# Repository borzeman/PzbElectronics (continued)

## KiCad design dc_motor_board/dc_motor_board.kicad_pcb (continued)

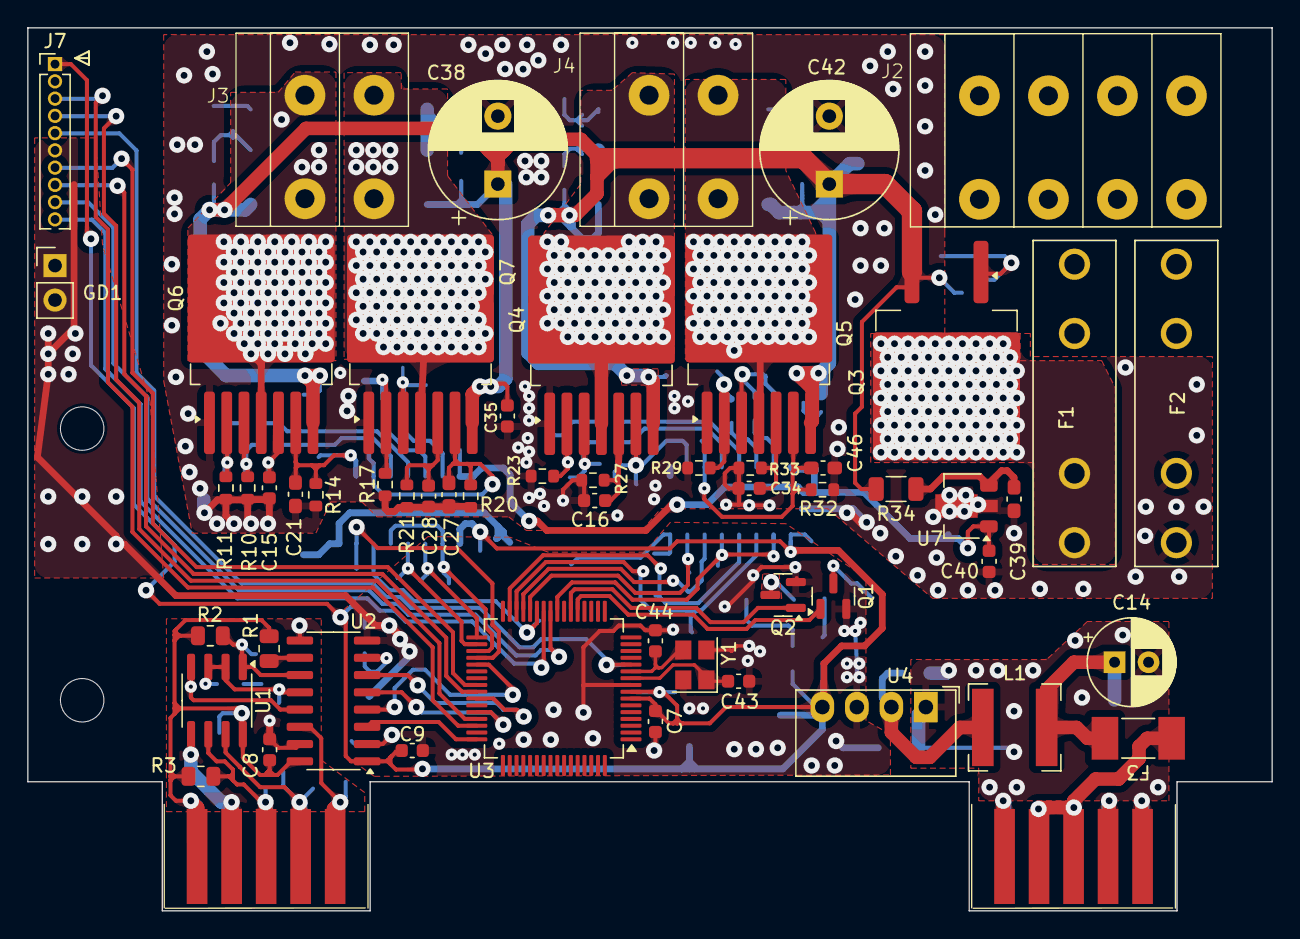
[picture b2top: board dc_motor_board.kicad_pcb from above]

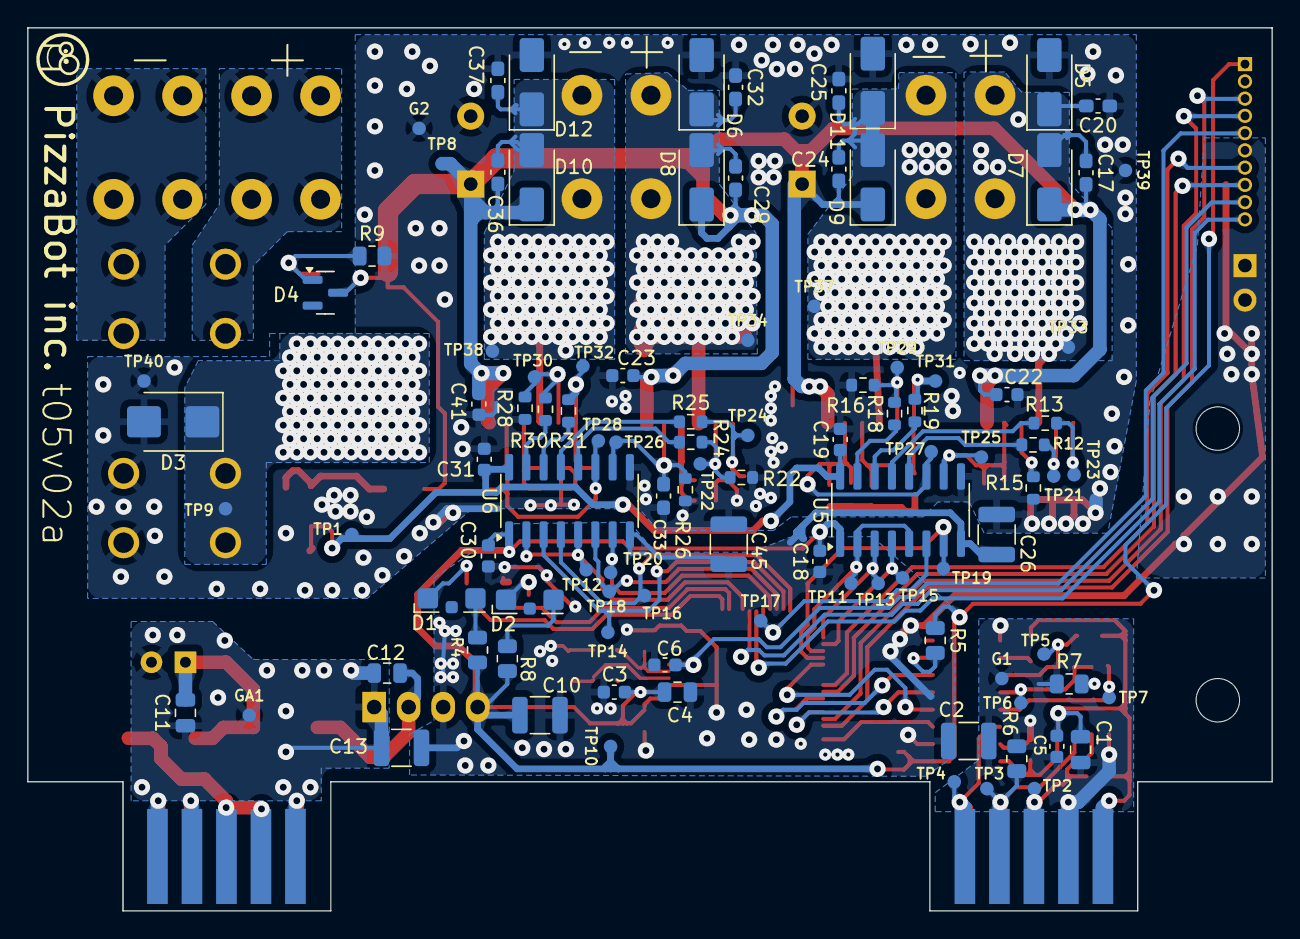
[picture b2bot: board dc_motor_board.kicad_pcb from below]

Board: 2 copper layers, 91.6 x 65.0 mm, 161 parts (102 on the bottom side), 81 nets.

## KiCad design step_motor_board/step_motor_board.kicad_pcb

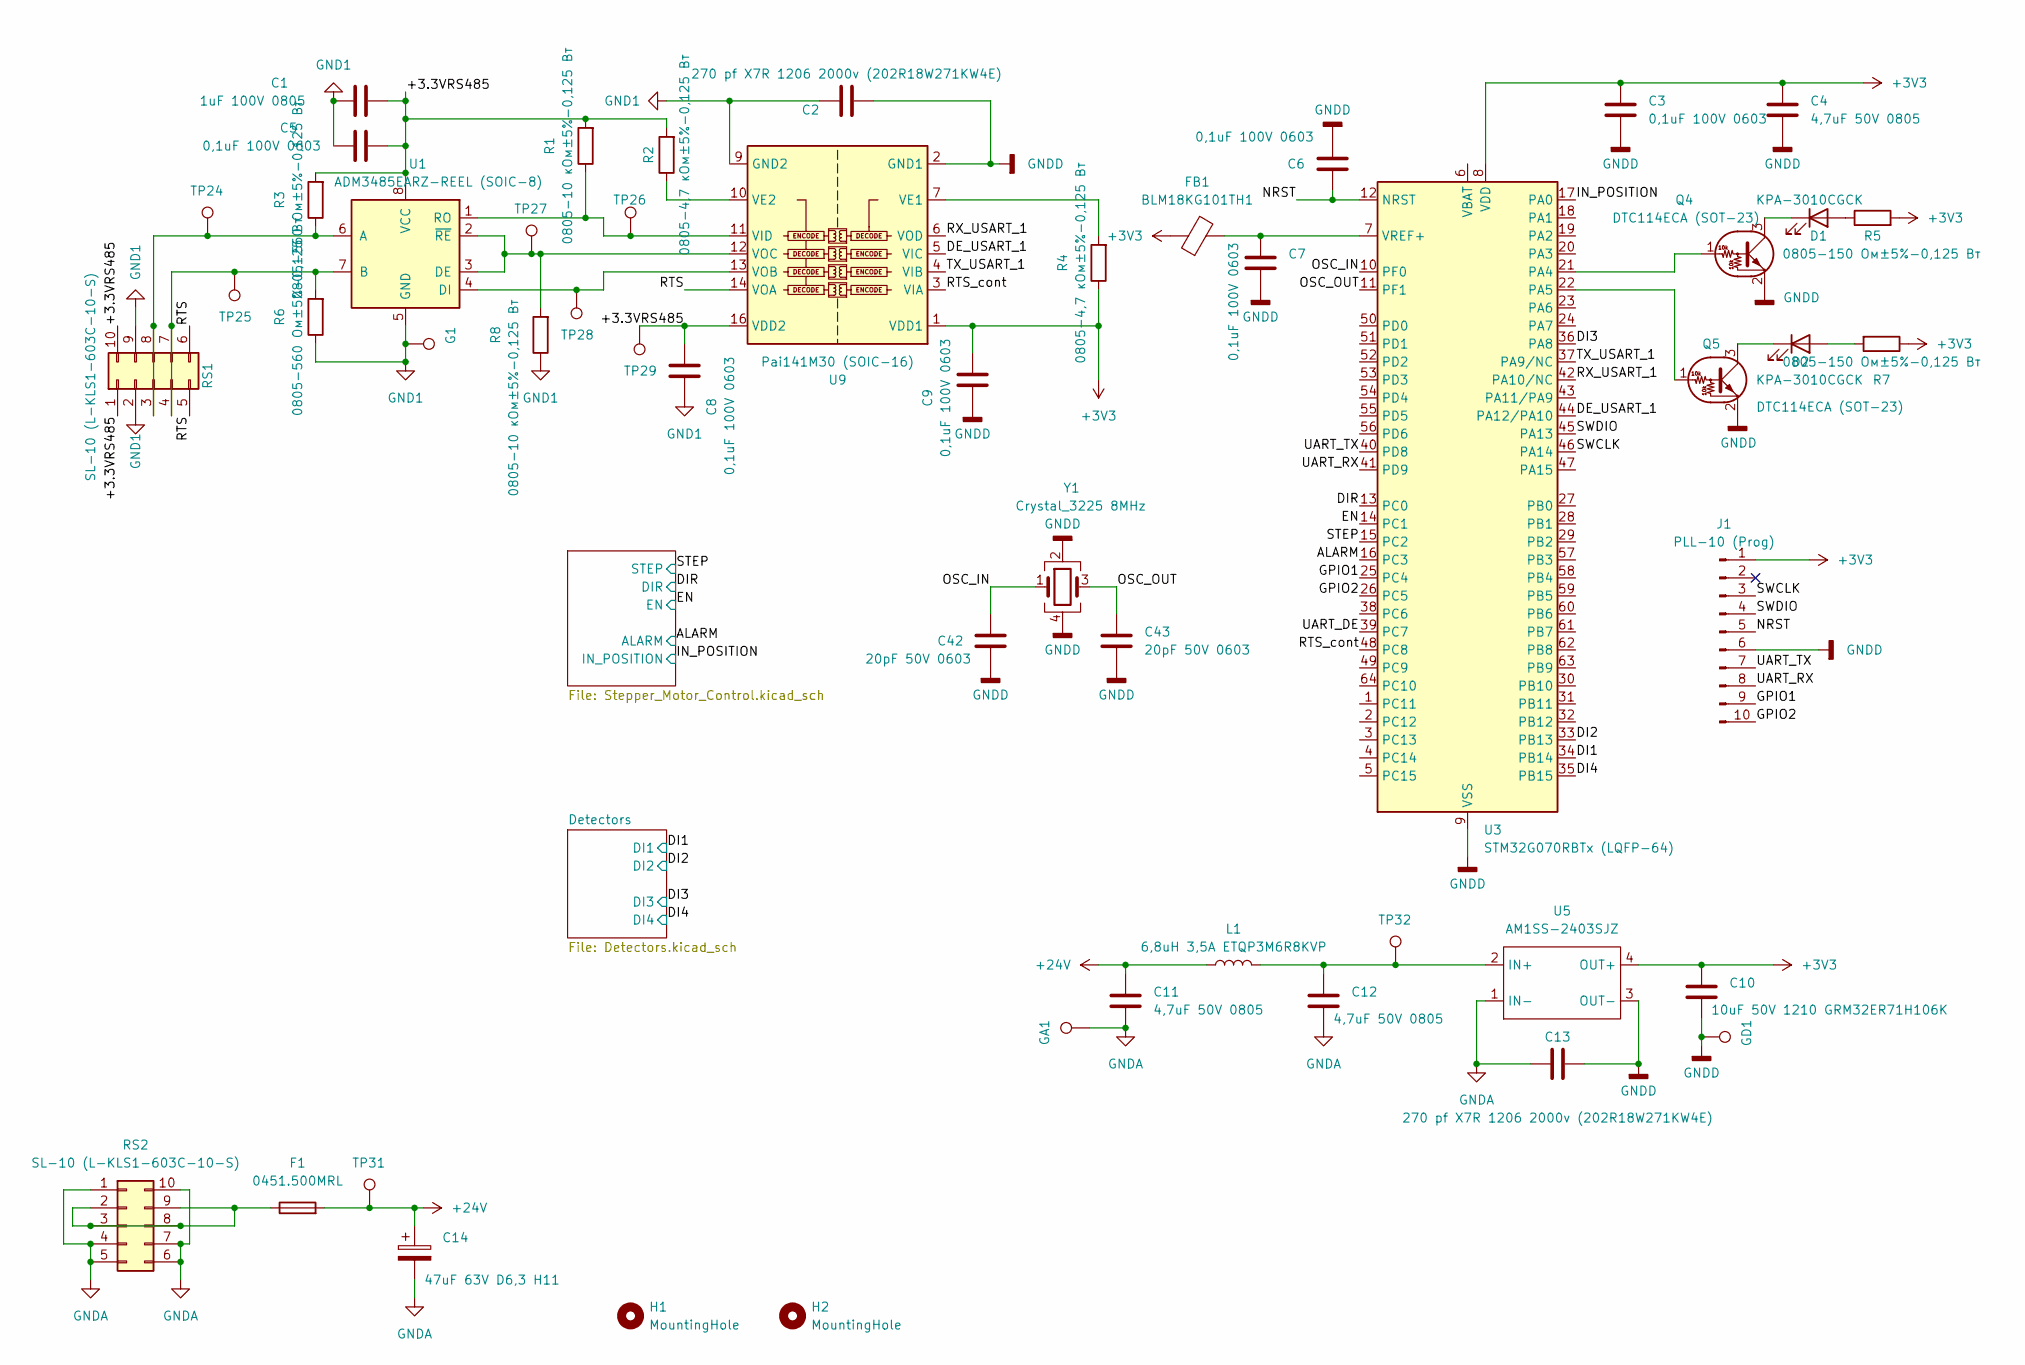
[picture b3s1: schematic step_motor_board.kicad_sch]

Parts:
C1: 1uF 100V 0805; C_0805_2012Metric
C2, C13: 270 pf X7R 1206 2000v (202R18W271KW4E); C_1210_3225Metric
C3, C5, C6, C7, C8, C9: 0,1uF 100V 0603; C_0603_1608Metric
C4, C11, C12: 4,7uF 50V 0805; C_0805_2012Metric
C10: 10uF 50V 1210 GRM32ER71H106K; C_1210_3225Metric
C14: 47uF 63V D6,3 H11; CP_Radial_D6.3mm_P2.50mm
C42, C43: 20pF 50V 0603; C_0603_1608Metric
D1, D2: KPA-3010CGCK; LED_Kingbright_KPA-3010_3x2x1mm
F1: 0451.500MRL; Fuse_Littelfuse-NANO2-451_453
FB1: BLM18KG101TH1; L_0603_1608Metric
G1: TestPoint; TestPoint_Pad_D1.0mm
GA1: TestPoint; TestPoint_Pad_D1.0mm
GD1: TestPoint; TestPoint_Pad_D1.0mm
H1, H2: MountingHole; MountingHole_3.2mm_M3
J1: PLL-10 (Prog); PinHeader_1x10_P1.27mm_Vertical
L1: 6,8uH 3,5A ETQP3M6R8KVP; L_Bourns-SRN6028
Q4, Q5: DTC114ECA (SOT-23); SOT-23
R1, R8: 0805-10 кОм±5%-0,125 Вт; R_0805_2012Metric
R2, R4: 0805-4,7 кОм±5%-0,125 Вт; R_0805_2012Metric
R3, R6: 0805-560 Ом±5%-0,125 Вт; R_0805_2012Metric
R5, R7: 0805-150 Ом±5%-0,125 Вт; R_0805_2012Metric
RS1, RS2: SL-10 (L-KLS1-603C-10-S); Edge_Conn_KLS1-603-10
TP24, TP25, TP26, TP27, TP28, TP29, TP31, TP32: TestPoint; TestPoint_Pad_D1.0mm
U1: ADM3485EARZ-REEL (SOIC-8); SOIC-8_3.9x4.9mm_P1.27mm
U3: STM32G070RBTx (LQFP-64); LQFP-64_10x10mm_P0.5mm
U5: AM1SS-2403SJZ; Converter_DCDC_Murata_MEE1SxxxxSC_THT
U9: Pai141M30 (SOIC-16); SOIC-16_3.9x9.9mm_P1.27mm
Y1: Crystal_3225 8MHz; Crystal_SMD_3225-4Pin_3.2x2.5mm

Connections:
+3V3: C3.1, C4.1, C9.2, C10.1, FB1.1, J1.1, R4.1, R5.2, R7.1, U3.8 (VDD), U5.4 (OUT+), U9.1 (VDD1); also elsewhere on the board
+24V: C11.1, C14.1, F1.2, L1.1, TP31.1; also elsewhere on the board
/+3.3VRS485: C1.2, C5.2, C8.2, R1.2, R2.2, R3.2, RS1.1, RS1.10, TP29.1, U1.8 (VCC), U9.16 (VDD2)
/ALARM: U3.16 (PC3); also elsewhere on the board
/DE_USART_1: U3.44 (PA12/PA10), U9.5 (VIC)
/DI1: U3.33 (PB13); also elsewhere on the board
/DI2: U3.34 (PB14); also elsewhere on the board
/DI3: U3.36 (PA8); also elsewhere on the board
/DI4: U3.35 (PB15); also elsewhere on the board
/DIR: U3.13 (PC0); also elsewhere on the board
/EN: U3.14 (PC1); also elsewhere on the board
/GPIO1: J1.9, U3.25 (PC4)
/GPIO2: J1.10, U3.26 (PC5)
/IN_POSITION: U3.17 (PA0); also elsewhere on the board
/NRST: C6.1, J1.5, U3.12 (NRST)
/OSC_IN: C42.1, U3.10 (PF0), Y1.1
/OSC_OUT: C43.1, U3.11 (PF1), Y1.3
/RTS: RS1.5, RS1.6, U9.14 (VOA)
/RTS_cont: U3.48 (PC8), U9.3 (VIA)
/RX_USART_1: U3.42 (PA10/NC), U9.6 (VOD)
/STEP: U3.15 (PC2); also elsewhere on the board
/SWCLK: J1.3, U3.46 (PA14)
/SWDIO: J1.4, U3.45 (PA13)
/TX_USART_1: U3.37 (PA9/NC), U9.4 (VIB)
/UART_DE: U3.39 (PC7)
/UART_RX: J1.8, U3.41 (PD9)
/UART_TX: J1.7, U3.40 (PD8)
GND1: C1.1, C2.1, C5.1, C8.1, G1.1, R6.1, R8.1, RS1.2, RS1.9, U1.5 (GND), U9.9 (GND2), U9.15 (GND2)
GNDA: C11.2, C12.2, C13.1, C14.2, GA1.1, RS2.1, RS2.4, RS2.5, RS2.6, RS2.7, RS2.10, U5.1 (IN-); also elsewhere on the board
GNDD: C2.2, C3.2, C4.2, C6.2, C7.2, C9.1, C10.2, C13.2, C42.2, C43.2, GD1.1, J1.6, Q4.2 (E), Q5.2 (E), U3.9 (VSS), U5.3 (OUT-), U9.2 (GND1), U9.8 (GND1), Y1.2, Y1.4; also elsewhere on the board
unnamed: D1.2 (A), R5.1
unnamed: D1.1 (K), Q4.3 (C)
unnamed: D2.2 (A), R7.2
unnamed: D2.1 (K), Q5.3 (C)
unnamed: Q4.1 (B), U3.21 (PA4)
unnamed: Q5.1 (B), U3.22 (PA5)
unnamed: R3.1, RS1.3, RS1.8, TP24.1, U1.6 (A)
unnamed: R6.2, RS1.4, RS1.7, TP25.1, U1.7 (B)
unnamed: F1.1, RS2.2, RS2.3, RS2.8, RS2.9
unnamed: R8.2, TP27.1, U1.2 (~RE), U1.3 (DE), U9.12 (VOC)
unnamed: TP28.1, U1.4 (DI), U9.13 (VOB)
unnamed: R1.1, TP26.1, U1.1 (RO), U9.11 (VID)
unnamed: C7.1, FB1.2, U3.7 (VREF+)
unnamed: C12.1, L1.2, TP32.1, U5.2 (IN+)
unnamed: R4.2, U9.7 (VE1)
unnamed: R2.1, U9.10 (VE2)

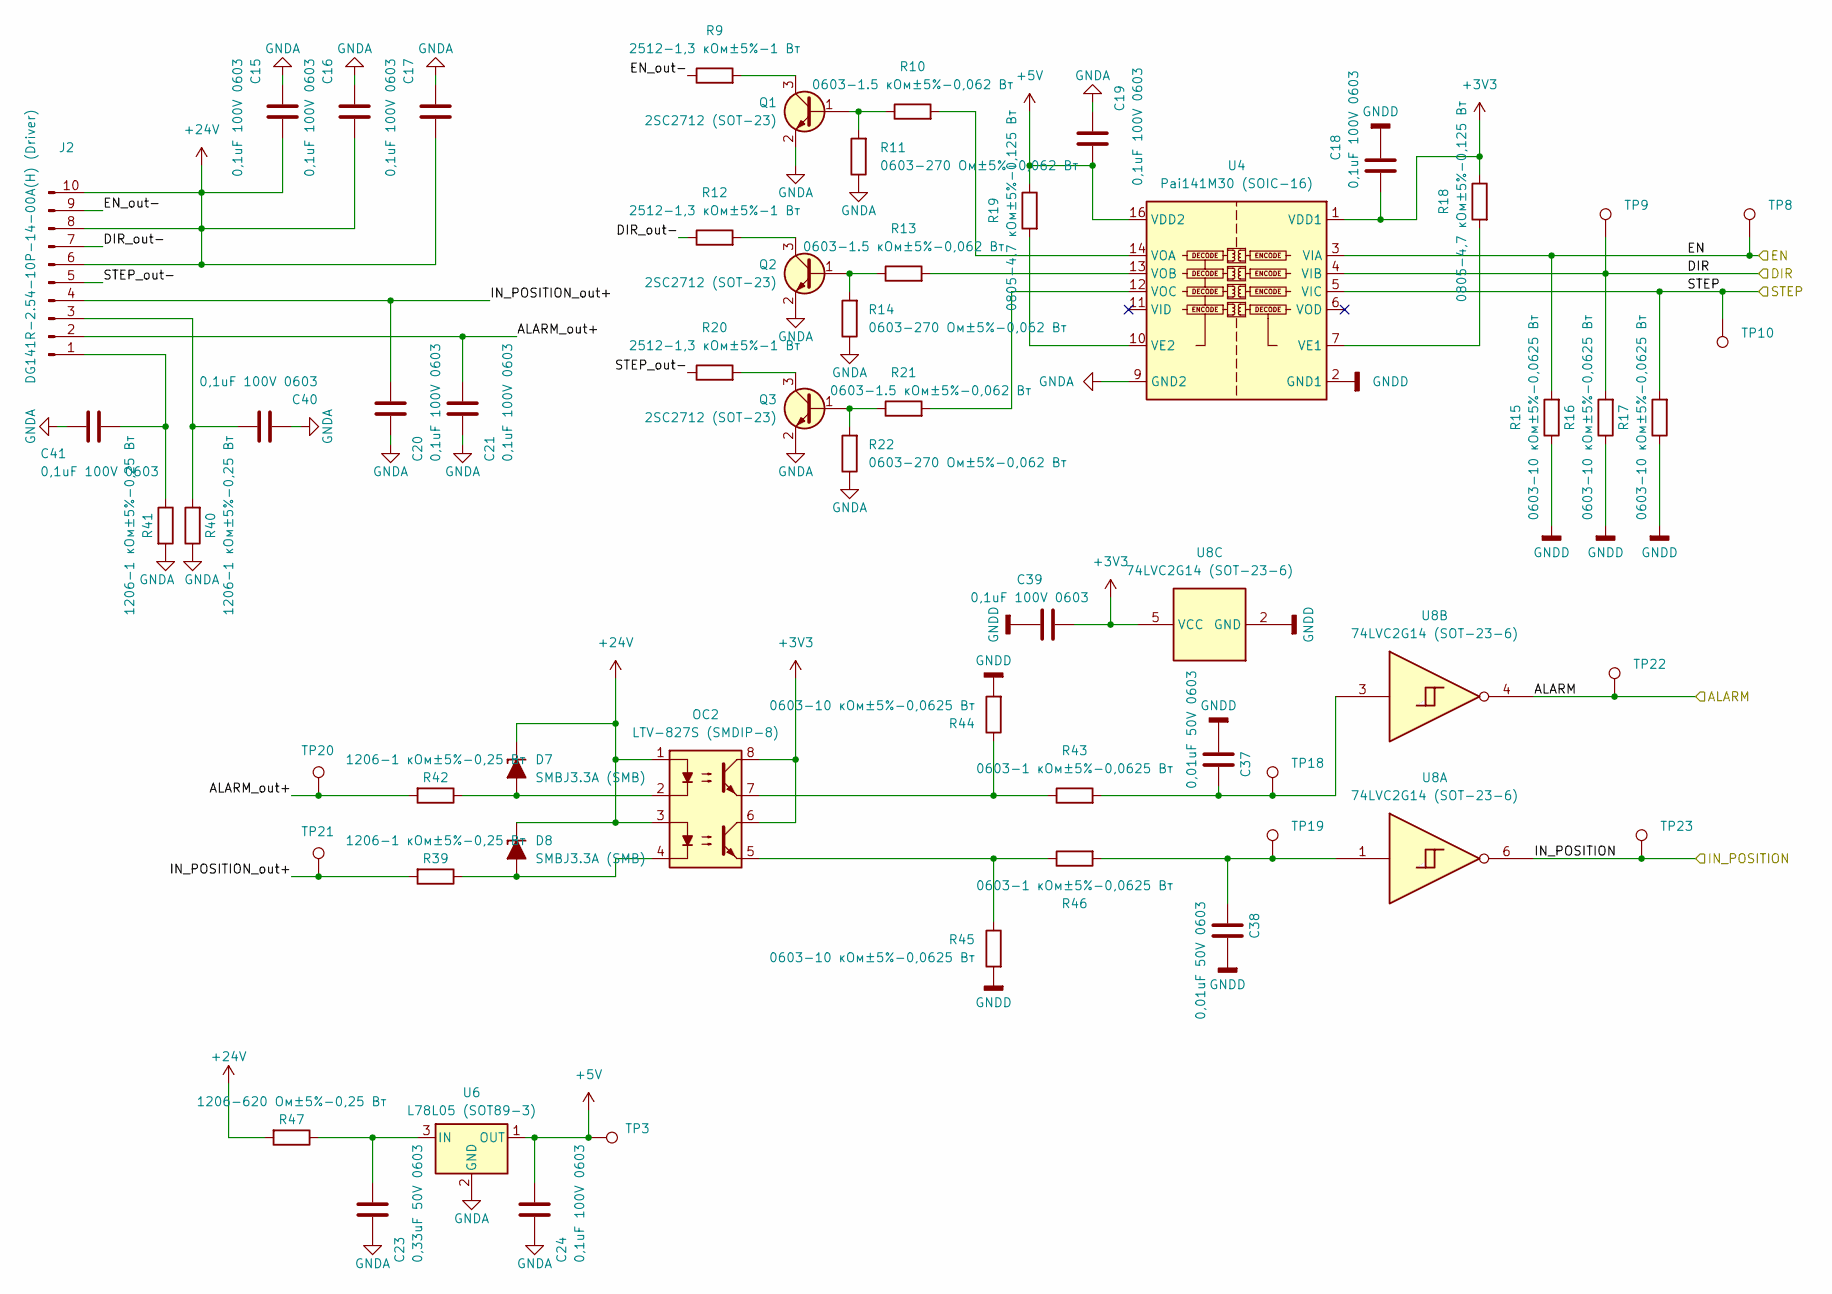
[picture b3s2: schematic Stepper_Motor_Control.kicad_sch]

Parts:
C15, C16, C17, C18, C19, C20, C21, C24, C39, C40, C41: 0,1uF 100V 0603; C_0603_1608Metric
C23: 0,33uF 50V 0603; C_0603_1608Metric
C37, C38: 0,01uF 50V 0603; C_0603_1608Metric
D7, D8: SMBJ3.3A (SMB); D_SMB
J2: DG141R-2.54-10P-14-00A(H) (Driver); DG141R-10
OC2: LTV-827S (SMDIP-8); SMDIP-8_W9.53mm
Q1, Q2, Q3: 2SC2712 (SOT-23); SOT-23
R9, R12, R20: 2512-1,3 кОм±5%-1 Вт; R_2512_6332Metric
R10, R13, R21: 0603-1.5 кОм±5%-0,062 Вт; R_0603_1608Metric
R11, R14, R22: 0603-270 Ом±5%-0,062 Вт; R_0603_1608Metric
R15, R16, R17, R44, R45: 0603-10 кОм±5%-0,0625 Вт; R_0603_1608Metric
R18, R19: 0805-4,7 кОм±5%-0,125 Вт; R_0805_2012Metric
R39, R40, R41, R42: 1206-1 кОм±5%-0,25 Вт; R_1206_3216Metric
R43, R46: 0603-1 кОм±5%-0,0625 Вт; R_0603_1608Metric
R47: 1206-620 Ом±5%-0,25 Вт; R_1206_3216Metric
TP3, TP8, TP9, TP10, TP18, TP19, TP20, TP21, TP22, TP23: TestPoint; TestPoint_Pad_D1.0mm
U4: Pai141M30 (SOIC-16); SOIC-16_3.9x9.9mm_P1.27mm
U6: L78L05 (SOT89-3); SOT-89-3
U8: 74LVC2G14 (SOT-23-6); SOT-23-6

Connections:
+3V3: C18.2, C39.2, OC2.6, OC2.8, R18.1, U4.1 (VDD1), U8.5 (VCC); also elsewhere on the board
+5V: C19.1, C24.1, R19.1, TP3.1, U4.16 (VDD2), U6.1 (OUT)
+24V: C15.1, C16.1, C17.1, D7.1 (K), D8.1 (K), J2.6, J2.8, J2.10, OC2.1, OC2.3, R47.2; also elsewhere on the board
/ALARM: TP22.1, U8.4; also elsewhere on the board
/DIR: R16.2, TP9.1, U4.4 (VIB); also elsewhere on the board
/EN: R15.2, TP8.1, U4.3 (VIA); also elsewhere on the board
/IN_POSITION: TP23.1, U8.6; also elsewhere on the board
/STEP: R17.2, TP10.1, U4.5 (VIC); also elsewhere on the board
/Stepper_Motor_Control/ALARM_out+: C21.1, J2.2, R42.2, TP20.1
/Stepper_Motor_Control/DIR_out-: J2.7, R12.1
/Stepper_Motor_Control/EN_out-: J2.9, R9.1
/Stepper_Motor_Control/IN_POSITION_out+: C20.1, J2.4, R39.2, TP21.1
/Stepper_Motor_Control/STEP_out-: J2.5, R20.1
GNDA: C15.2, C16.2, C17.2, C19.2, C20.2, C21.2, C23.2, C24.2, C40.2, C41.2, Q1.2 (E), Q2.2 (E), Q3.2 (E), R11.1, R14.1, R22.1, R40.1, R41.2, U4.9 (GND2), U4.15 (GND2), U6.2 (GND); also elsewhere on the board
GNDD: C18.1, C37.2, C38.2, C39.1, R15.1, R16.1, R17.1, R44.2, R45.2, U4.2 (GND1), U4.8 (GND1), U8.2 (GND); also elsewhere on the board
unnamed: C37.1, R43.2, TP18.1, U8.3
unnamed: C38.1, R46.2, TP19.1, U8.1
unnamed: D7.2 (A), OC2.2, R42.1
unnamed: D8.2 (A), OC2.4, R39.1
unnamed: C41.1, J2.1, R41.1
unnamed: C40.1, J2.3, R40.2
unnamed: OC2.5, R45.1, R46.1
unnamed: OC2.7, R43.1, R44.1
unnamed: Q1.1 (B), R10.1, R11.2
unnamed: Q1.3 (C), R9.2
unnamed: Q2.1 (B), R13.1, R14.2
unnamed: Q2.3 (C), R12.2
unnamed: Q3.1 (B), R21.1, R22.2
unnamed: Q3.3 (C), R20.2
unnamed: R18.2, U4.7 (VE1)
unnamed: R19.2, U4.10 (VE2)
unnamed: R10.2, U4.14 (VOA)
unnamed: R13.2, U4.13 (VOB)
unnamed: R21.2, U4.12 (VOC)
unnamed: C23.1, R47.1, U6.3 (IN)

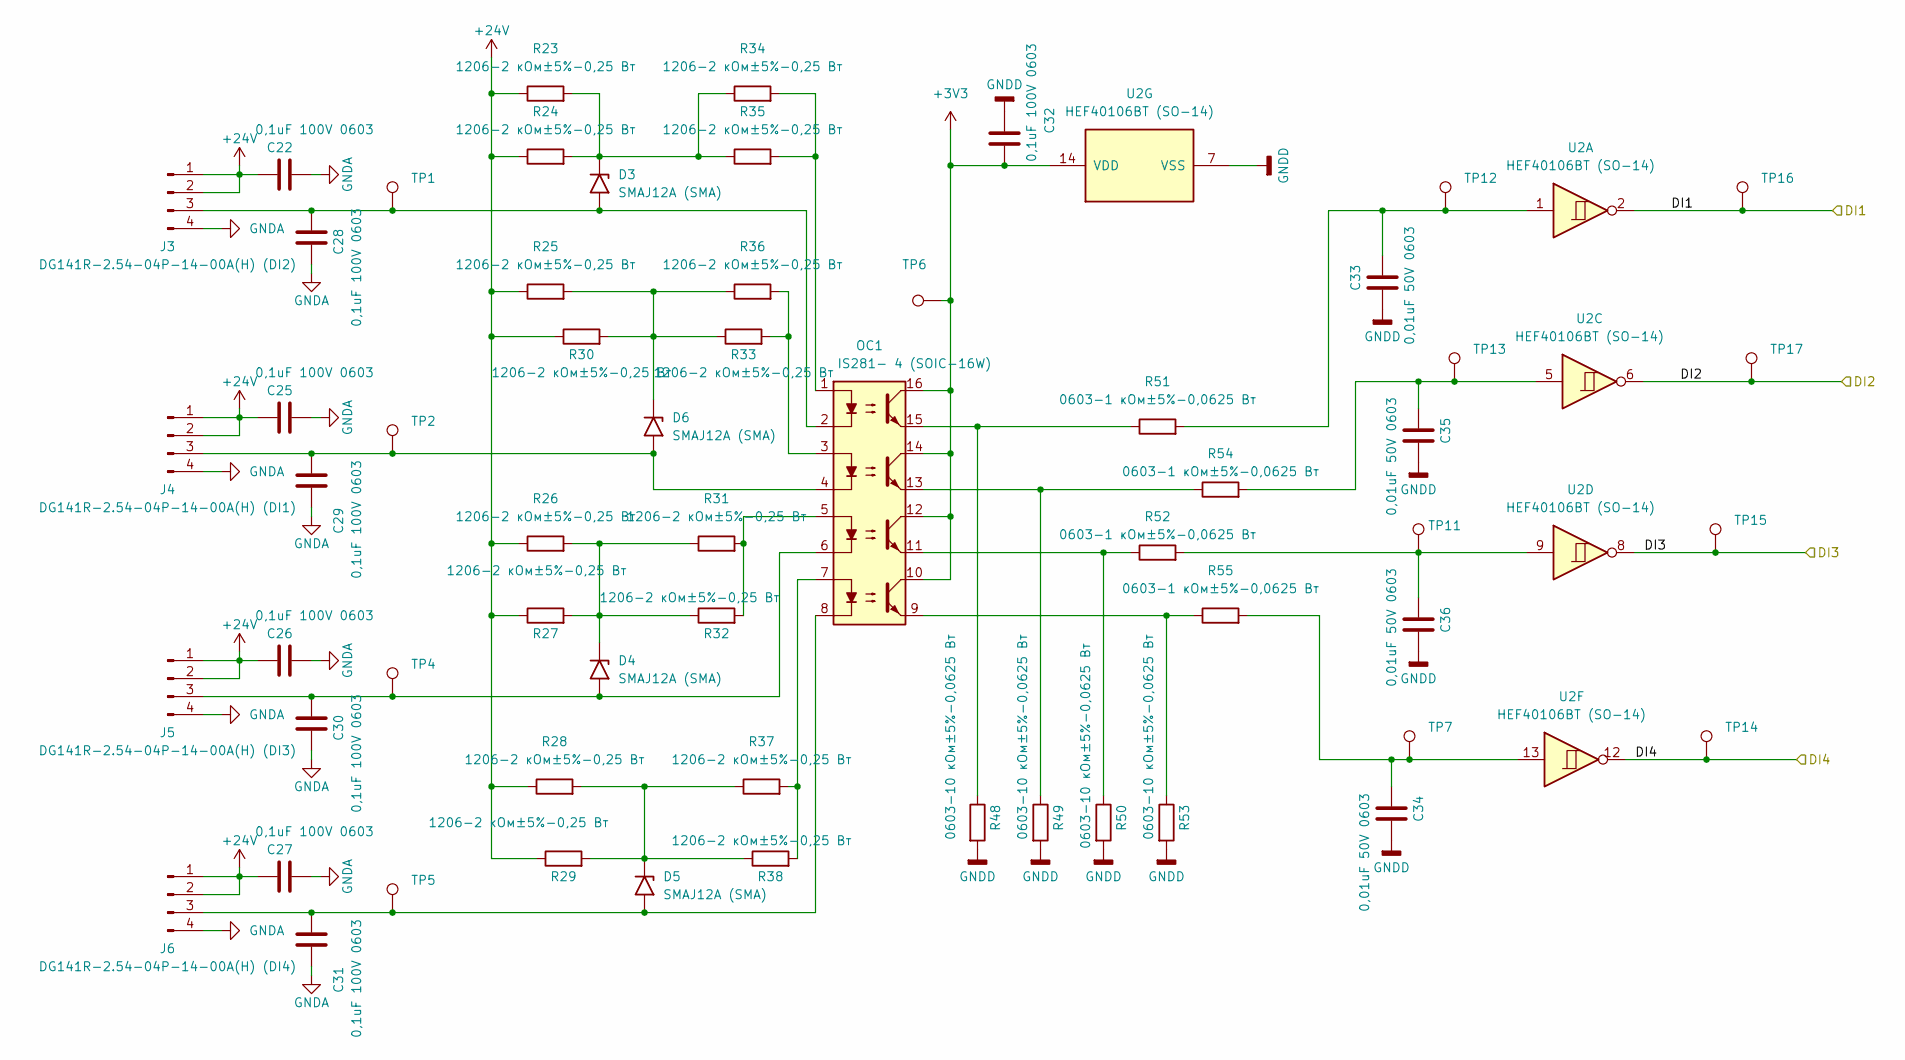
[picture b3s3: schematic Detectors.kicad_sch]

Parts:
C22, C25, C26, C27, C28, C29, C30, C31, C32: 0,1uF 100V 0603; C_0603_1608Metric
C33, C34, C35, C36: 0,01uF 50V 0603; C_0603_1608Metric
D3, D4, D5, D6: SMAJ12A (SMA); D_SMA
J3: DG141R-2.54-04P-14-00A(H) (DI2); DG141R-04
J4: DG141R-2.54-04P-14-00A(H) (DI1); DG141R-04
J5: DG141R-2.54-04P-14-00A(H) (DI3); DG141R-04
J6: DG141R-2.54-04P-14-00A(H) (DI4); DG141R-04
OC1: IS281- 4 (SOIC-16W); SOIC-16W_5.3x10.2mm_P1.27mm
R23, R24, R25, R26, R27, R28, R29, R30, R31, R32, R33, R34, R35, R36, R37, R38: 1206-2 кОм±5%-0,25 Вт; R_1206_3216Metric
R48, R49, R50, R53: 0603-10 кОм±5%-0,0625 Вт; R_0603_1608Metric
R51, R52, R54, R55: 0603-1 кОм±5%-0,0625 Вт; R_0603_1608Metric
TP1, TP2, TP4, TP5, TP6, TP7, TP11, TP12, TP13, TP14, TP15, TP16, TP17: TestPoint; TestPoint_Pad_D1.0mm
U2: HEF40106BT (SO-14); SO-14_5.3x10.2mm_P1.27mm

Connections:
+3V3: C32.2, OC1.10, OC1.12, OC1.14, OC1.16, TP6.1, U2.14 (VDD); also elsewhere on the board
+24V: C22.1, C25.1, C26.1, C27.1, J3.1, J3.2, J4.1, J4.2, J5.1, J5.2, J6.1, J6.2, R23.1, R24.1, R25.1, R26.1, R27.1, R28.1, R29.1, R30.1; also elsewhere on the board
/DI1: TP17.1, U2.6; also elsewhere on the board
/DI2: TP16.1, U2.2; also elsewhere on the board
/DI3: TP15.1, U2.8; also elsewhere on the board
/DI4: TP14.1, U2.12; also elsewhere on the board
GNDA: C22.2, C25.2, C26.2, C27.2, C28.2, C29.2, C30.2, C31.2, J3.4, J4.4, J5.4, J6.4; also elsewhere on the board
GNDD: C32.1, C33.2, C34.2, C35.2, C36.2, R48.2, R49.2, R50.2, R53.2, U2.7 (VSS); also elsewhere on the board
unnamed: C33.1, R51.2, TP12.1, U2.1
unnamed: C34.1, R55.2, TP7.1, U2.13
unnamed: C35.1, R54.2, TP13.1, U2.5
unnamed: C36.1, R52.2, TP11.1, U2.9
unnamed: D3.1 (A1), R23.2, R24.2, R34.1, R35.1
unnamed: C28.1, D3.2 (A2), J3.3, OC1.2, TP1.1
unnamed: D4.1 (A1), R26.2, R27.2, R31.1, R32.1
unnamed: C30.1, D4.2 (A2), J5.3, OC1.6, TP4.1
unnamed: D5.1 (A1), R28.2, R29.2, R37.1, R38.1
unnamed: C31.1, D5.2 (A2), J6.3, OC1.8, TP5.1
unnamed: D6.1 (A1), R25.2, R30.2, R33.1, R36.1
unnamed: C29.1, D6.2 (A2), J4.3, OC1.4, TP2.1
unnamed: OC1.1, R34.2, R35.2
unnamed: OC1.3, R33.2, R36.2
unnamed: OC1.5, R31.2, R32.2
unnamed: OC1.7, R37.2, R38.2
unnamed: OC1.9, R53.1, R55.1
unnamed: OC1.11, R50.1, R52.1
unnamed: OC1.13, R49.1, R54.1
unnamed: OC1.15, R48.1, R51.1

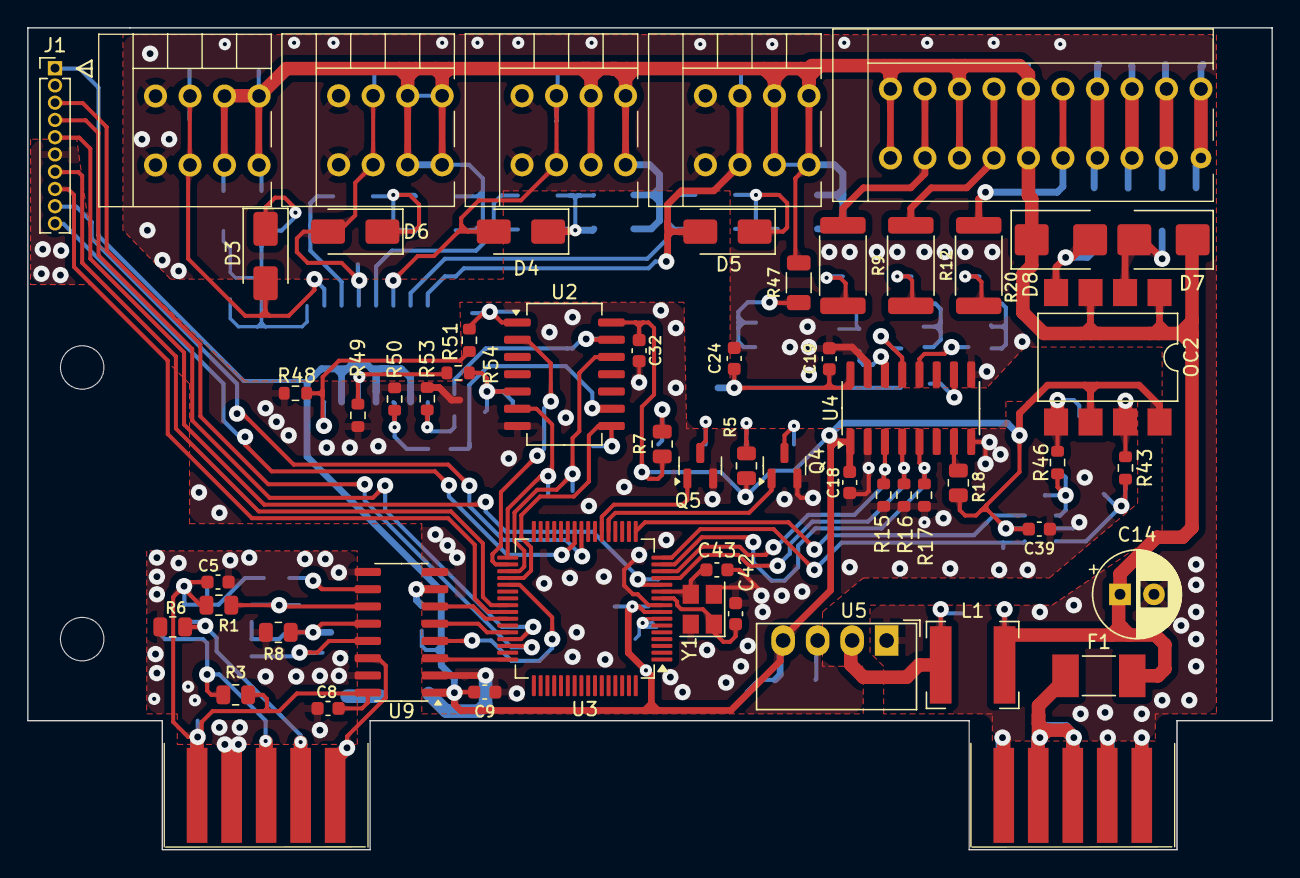
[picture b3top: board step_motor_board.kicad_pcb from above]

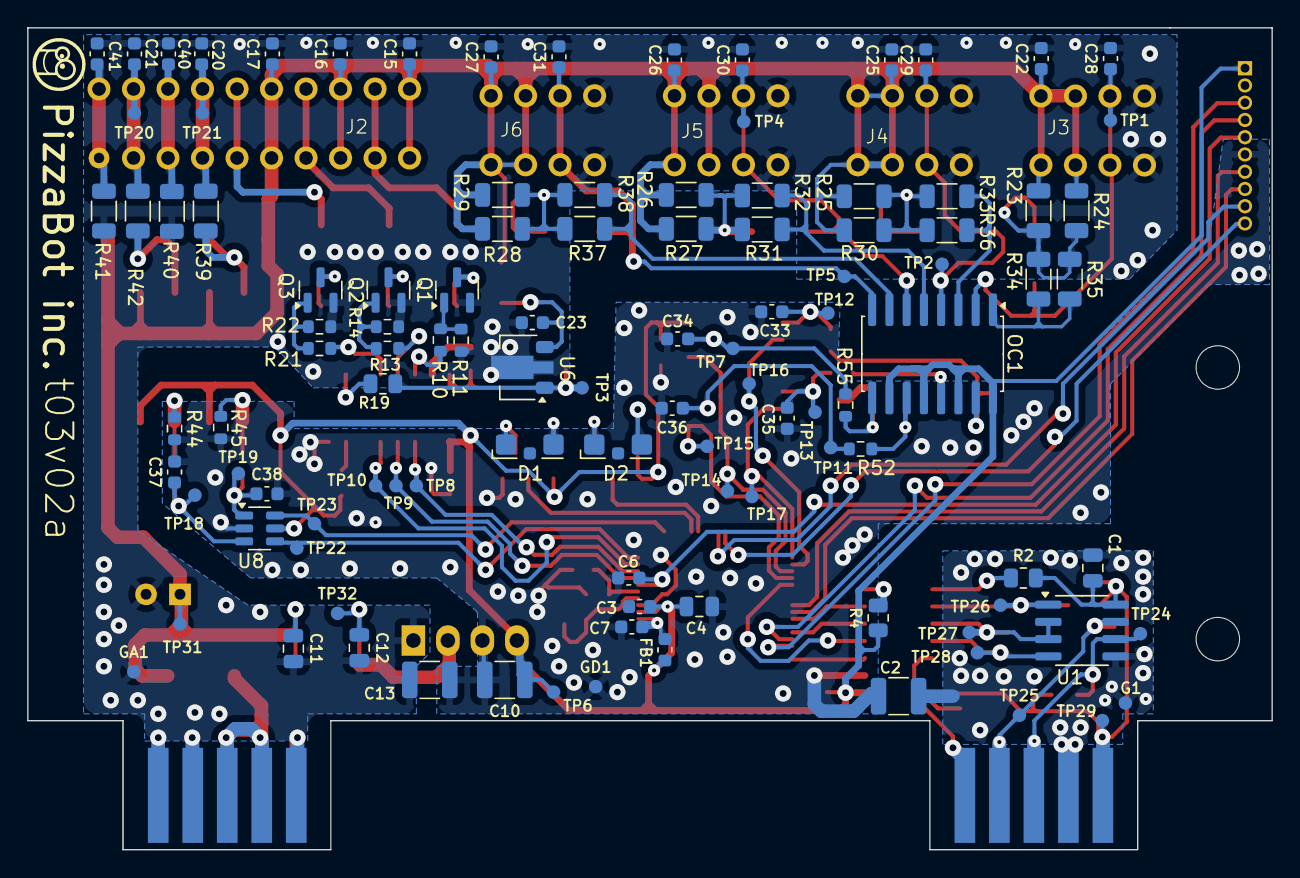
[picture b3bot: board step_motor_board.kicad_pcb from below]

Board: 2 copper layers, 91.6 x 60.5 mm, 169 parts (109 on the bottom side), 91 nets.

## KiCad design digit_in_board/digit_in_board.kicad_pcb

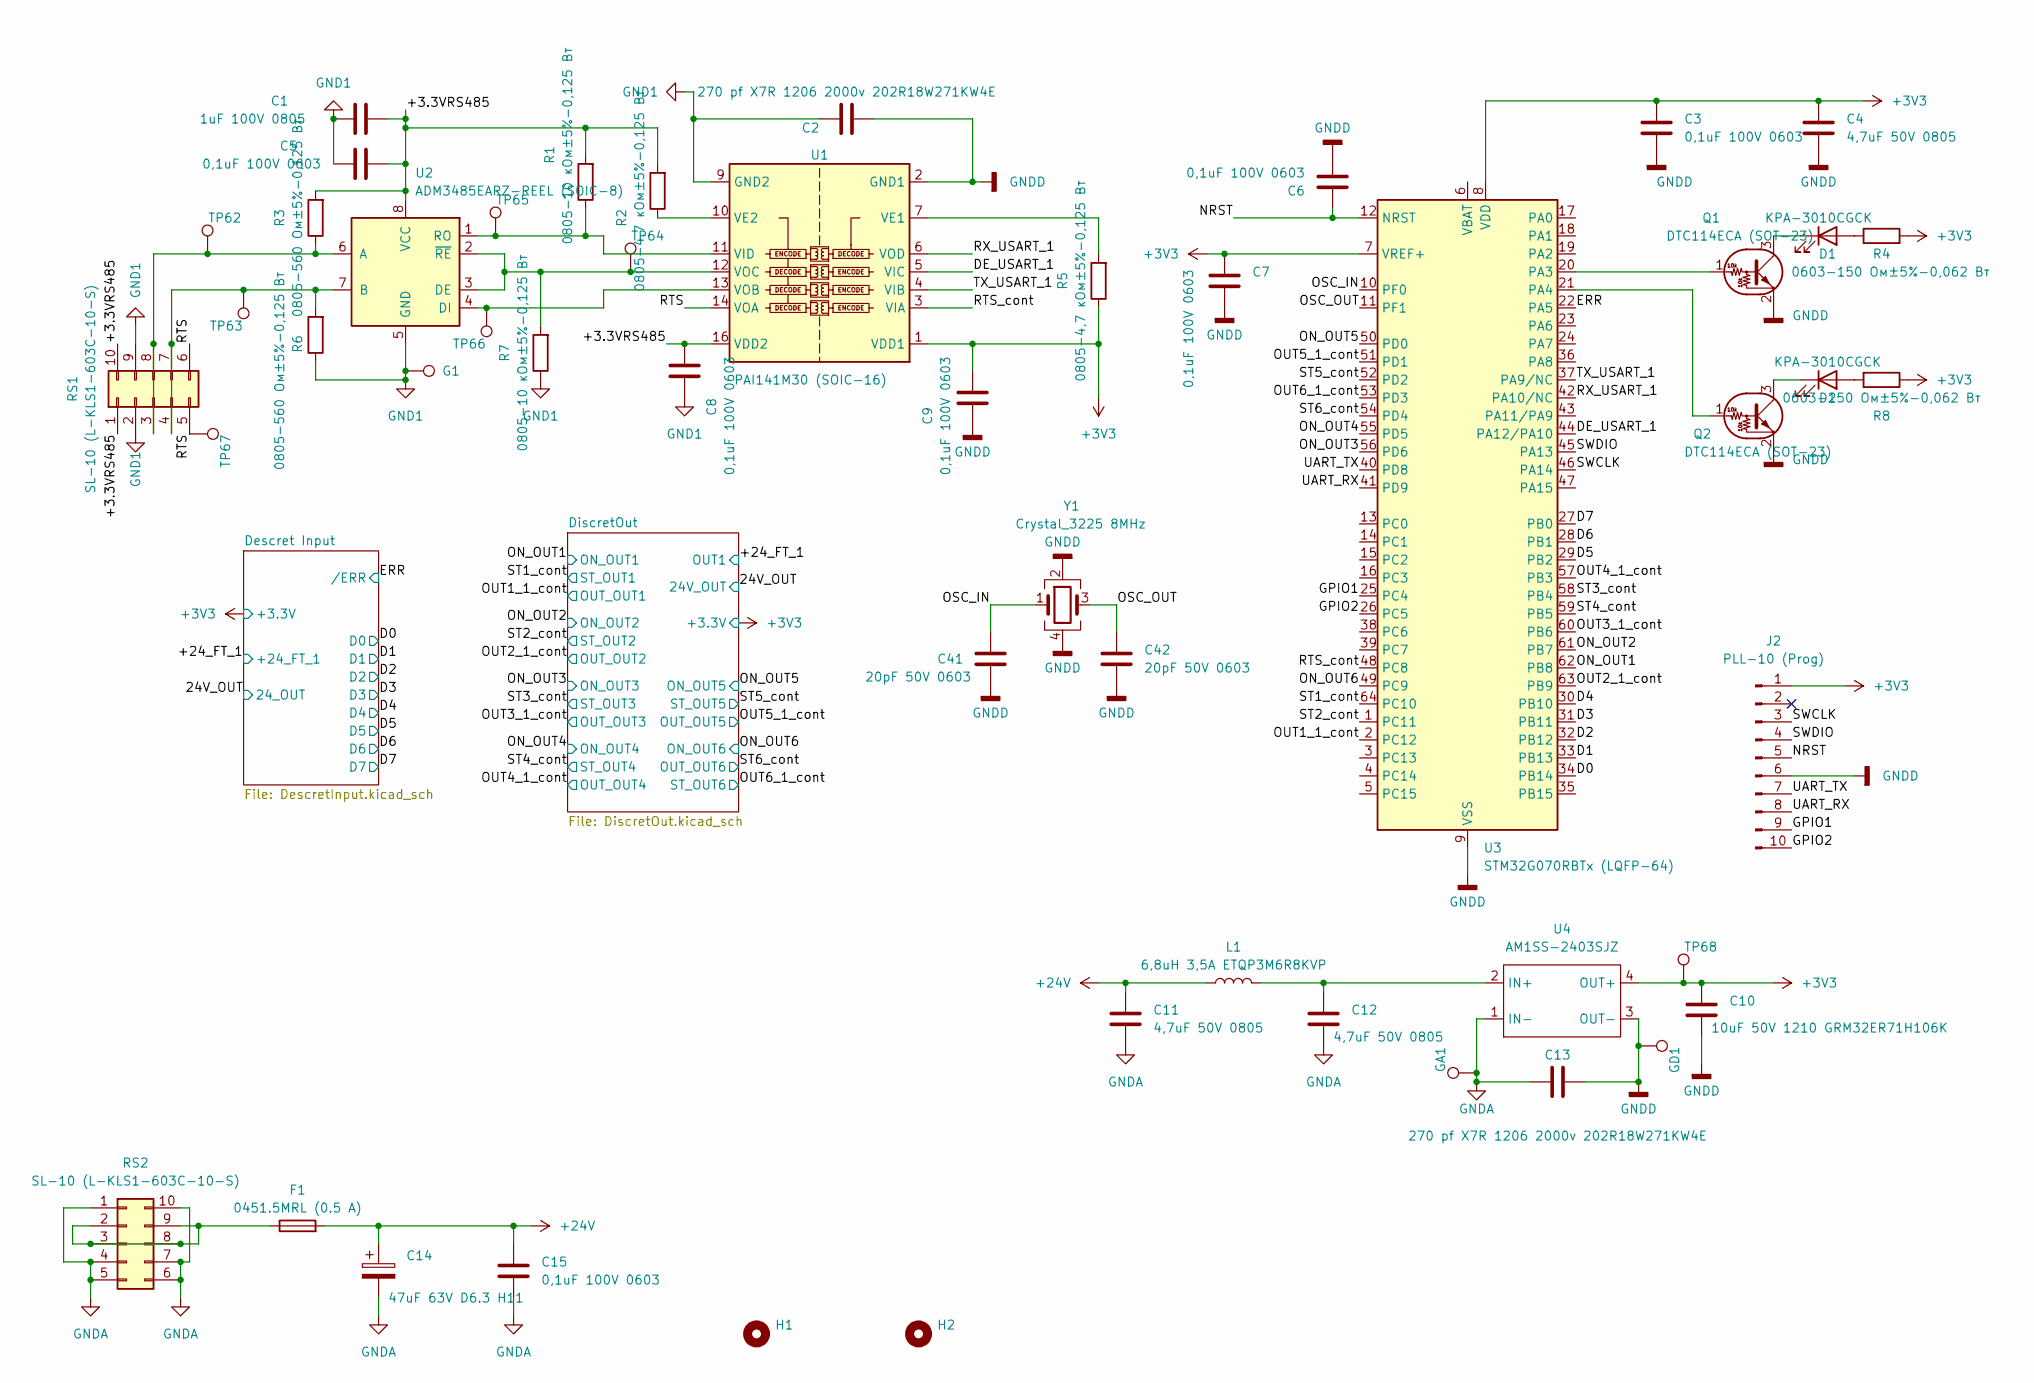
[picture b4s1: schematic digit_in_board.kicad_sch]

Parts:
C1: 1uF 100V 0805; C_0805_2012Metric_Pad1.18x1.45mm_HandSolder
C2, C13: 270 pf X7R 1206 2000v 202R18W271KW4E; C_1210_3225Metric_Pad1.42x2.65mm
C3, C5, C6, C7, C8, C9, C15: 0,1uF 100V 0603; C_0603_1608Metric
C4, C11, C12: 4,7uF 50V 0805; C_0805_2012Metric_Pad1.18x1.45mm_HandSolder
C10: 10uF 50V 1210 GRM32ER71H106K; C_1210_3225Metric_Pad1.42x2.65mm_HandSolder
C14: 47uF 63V D6.3 H11; CP_Radial_D6.3mm_P2.50mm
C41, C42: 20pF 50V 0603; C_0603_1608Metric
D1, D2: KPA-3010CGCK; LED_Kingbright_KPA-3010_3x2x1mm
F1: 0451.5MRL (0.5 А); Fuse_Littelfuse-NANO2-451_453
G1: TestPoint_D1
GA1: TestPoint_D1
GD1: TestPoint_D1
H1, H2: MountingHole; MountingHole_3.2mm_M3
J2: PLL-10 (Prog); PinHeader_1x10_P1.27mm_Vertical
L1: 6,8uH 3,5A ETQP3M6R8KVP; L_Bourns-SRN6028
Q1, Q2: DTC114ECA (SOT-23); SOT-23
R1, R7: 0805-10 кОм±5%-0,125 Вт; R_0805_2012Metric
R2, R5: 0805-4,7 кОм±5%-0,125 Вт; R_0805_2012Metric
R3, R6: 0805-560 Ом±5%-0,125 Вт; R_0805_2012Metric
R4, R8: 0603-150 Ом±5%-0,062 Вт; R_0603
RS1, RS2: SL-10 (L-KLS1-603C-10-S); Edge_Conn_KLS1-603-10
TP62, TP63, TP64, TP65, TP66, TP67, TP68: TestPoint_D1
U1: PAI141M30 (SOIC-16); SOIC-16_3.9x9.9mm_P1.27mm
U2: ADM3485EARZ-REEL (SOIC-8); SOIC-8_3.9x4.9mm_P1.27mm
U3: STM32G070RBTx (LQFP-64); LQFP-64_10x10mm_P0.5mm
U4: AM1SS-2403SJZ; Converter_DCDC_Murata_MEE1SxxxxSC_THT
Y1: Crystal_3225 8MHz; Crystal_SMD_3225-4Pin_3.2x2.5mm

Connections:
+3V3: C3.1, C4.1, C7.1, C9.2, C10.1, J2.1, R4.2, R5.1, R8.1, TP68.1, U1.1 (VDD1), U3.7 (VREF+), U3.8 (VDD), U4.4 (OUT+); also elsewhere on the board
/+3.3VRS485: C1.2, C5.2, C8.2, R1.2, R2.2, R3.2, RS1.1, RS1.10, U1.16 (VDD2), U2.8 (VCC)
/D0: U3.34 (PB14); also elsewhere on the board
/D1: U3.33 (PB13); also elsewhere on the board
/D2: U3.32 (PB12); also elsewhere on the board
/D3: U3.31 (PB11); also elsewhere on the board
/D4: U3.30 (PB10); also elsewhere on the board
/D5: U3.29 (PB2); also elsewhere on the board
/D6: U3.28 (PB1); also elsewhere on the board
/D7: U3.27 (PB0); also elsewhere on the board
/DE_USART_1: U1.5 (VIC), U3.44 (PA12/PA10)
/ERR: U3.22 (PA5); also elsewhere on the board
/GPIO1: J2.9, U3.25 (PC4)
/GPIO2: J2.10, U3.26 (PC5)
/NRST: C6.1, J2.5, U3.12 (NRST)
/ON_OUT1: U3.62 (PB8); also elsewhere on the board
/ON_OUT2: U3.61 (PB7); also elsewhere on the board
/ON_OUT3: U3.56 (PD6); also elsewhere on the board
/ON_OUT4: U3.55 (PD5); also elsewhere on the board
/ON_OUT5: U3.50 (PD0); also elsewhere on the board
/ON_OUT6: U3.49 (PC9); also elsewhere on the board
/OSC_IN: C41.1, U3.10 (PF0), Y1.1
/OSC_OUT: C42.1, U3.11 (PF1), Y1.3
/OUT1_1_cont: U3.2 (PC12); also elsewhere on the board
/OUT2_1_cont: U3.63 (PB9); also elsewhere on the board
/OUT3_1_cont: U3.60 (PB6); also elsewhere on the board
/OUT4_1_cont: U3.57 (PB3); also elsewhere on the board
/OUT5_1_cont: U3.51 (PD1); also elsewhere on the board
/OUT6_1_cont: U3.53 (PD3); also elsewhere on the board
/RTS: RS1.5, RS1.6, TP67.1, U1.14 (VOA)
/RTS_cont: U1.3 (VIA), U3.48 (PC8)
/RX_USART_1: U1.6 (VOD), U3.42 (PA10/NC)
/ST1_cont: U3.64 (PC10); also elsewhere on the board
/ST2_cont: U3.1 (PC11); also elsewhere on the board
/ST3_cont: U3.58 (PB4); also elsewhere on the board
/ST4_cont: U3.59 (PB5); also elsewhere on the board
/ST5_cont: U3.52 (PD2); also elsewhere on the board
/ST6_cont: U3.54 (PD4); also elsewhere on the board
/SWCLK: J2.3, U3.46 (PA14)
/SWDIO: J2.4, U3.45 (PA13)
/TX_USART_1: U1.4 (VIB), U3.37 (PA9/NC)
/UART_RX: J2.8, U3.41 (PD9)
/UART_TX: J2.7, U3.40 (PD8)
GNDA: C11.2, C12.2, C13.1, C14.2, C15.2, GA1.1, RS2.1, RS2.4, RS2.5, RS2.6, RS2.7, RS2.10, U4.1 (IN-)
unnamed: D1.2 (A), R4.1
unnamed: D1.1 (K), Q1.3 (C)
unnamed: D2.2 (A), R8.2
unnamed: Q1.1 (B), U3.20 (PA3)
unnamed: R3.1, RS1.3, RS1.8, TP62.1, U2.6 (A)
unnamed: R6.2, RS1.4, RS1.7, TP63.1, U2.7 (B)
unnamed: R5.2, U1.7 (VE1)
unnamed: R2.1, U1.10 (VE2)
unnamed: R1.1, TP65.1, U1.11 (VID), U2.1 (RO)
unnamed: TP66.1, U1.13 (VOB), U2.4 (DI)
unnamed: C12.1, L1.2, U4.2 (IN+)
